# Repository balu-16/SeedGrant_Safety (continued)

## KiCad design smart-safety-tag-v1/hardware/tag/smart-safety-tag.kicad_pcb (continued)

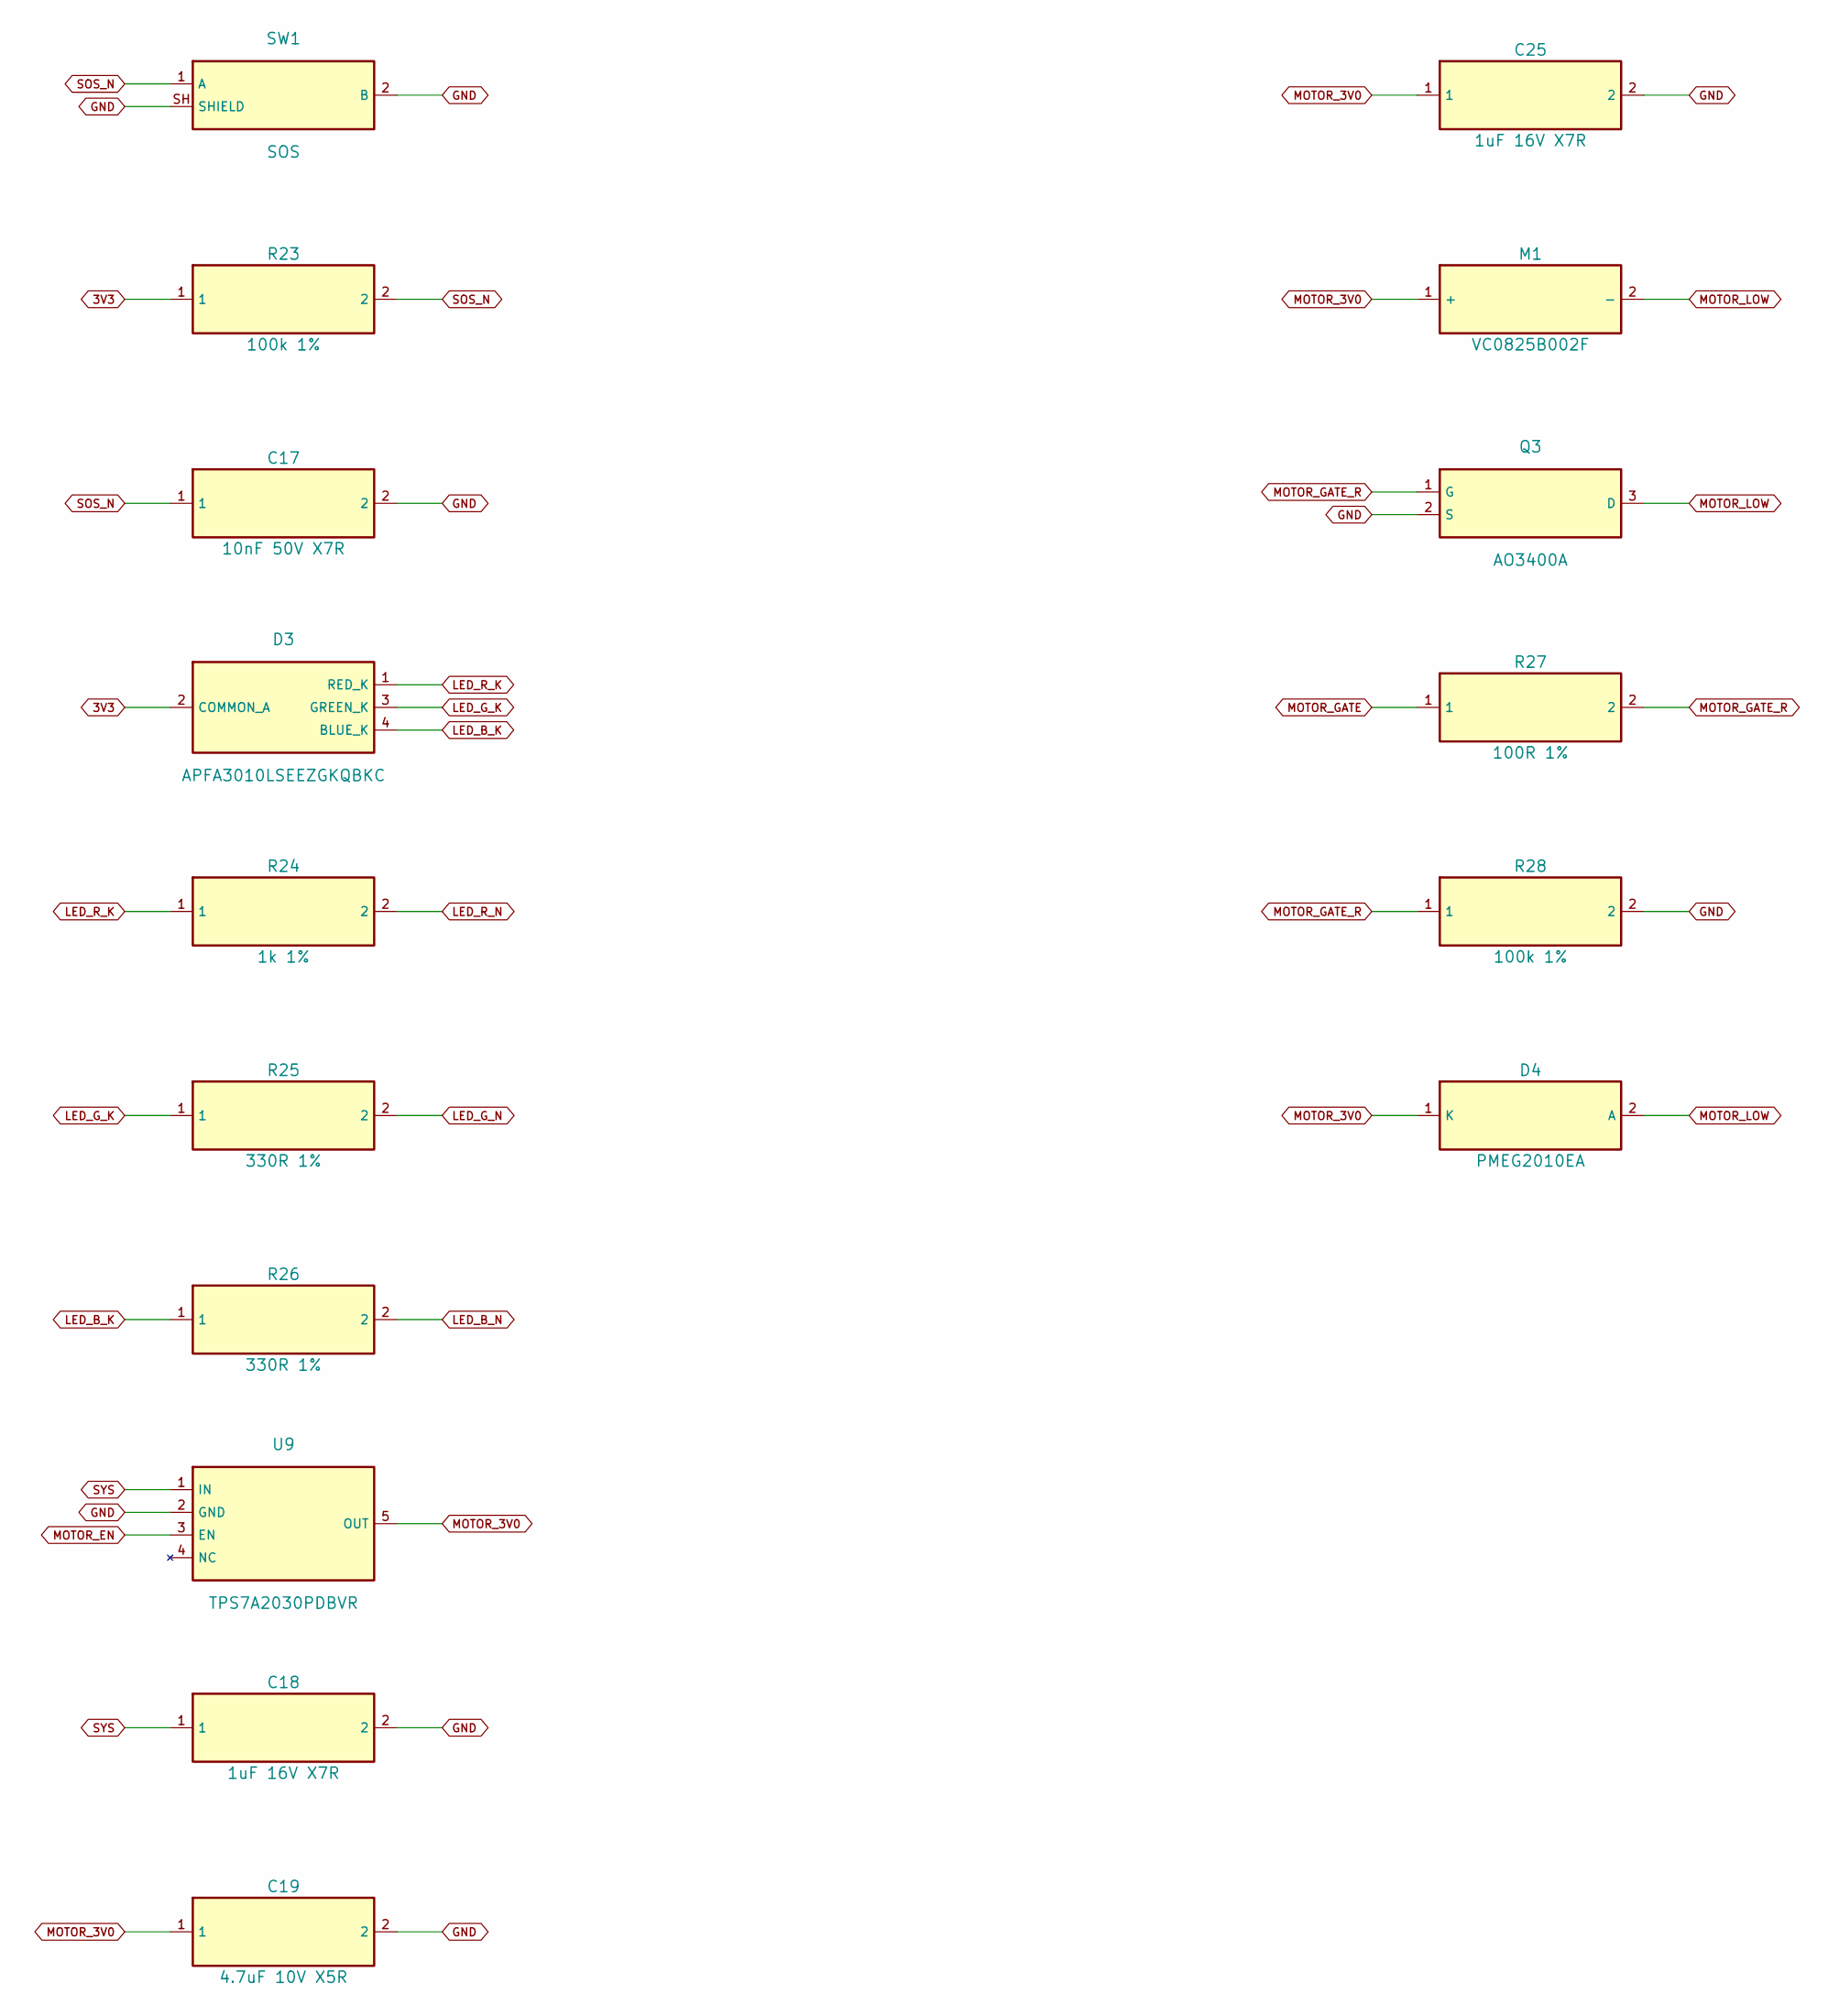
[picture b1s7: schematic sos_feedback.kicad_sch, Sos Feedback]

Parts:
C17: 10nF 50V X7R; C_0603_1608Metric; MPN C1608X7R1H103K080AA
C18, C25: 1uF 16V X7R; C_0603_1608Metric; MPN C1608X7R1C105K080AC
C19: 4.7uF 10V X5R; C_0603_1608Metric; MPN C1608X5R1A475K080AE
D3: APFA3010LSEEZGKQBKC; LED_Kingbright_APFA3010_3x1.5mm_Horizontal; MPN APFA3010LSEEZGKQBKC
D4: PMEG2010EA; D_SOD-323; MPN PMEG2010EA,115
M1: VC0825B002F; Motor_VC0825B002F; MPN VC0825B002F
Q3: AO3400A; SOT-23; MPN AO3400A
R23, R28: 100k 1%; R_0603_1608Metric; MPN RC0603FR-07100KL
R24: 1k 1%; R_0603_1608Metric; MPN RC0603FR-071KL
R25, R26: 330R 1%; R_0603_1608Metric; MPN RC0603FR-07330RL
R27: 100R 1%; R_0603_1608Metric; MPN RC0603FR-07100RL
SW1: SOS; SW_Push_1P1T-SH_NO_CK_KMR2xxG; MPN KMR231GLFS
U9: TPS7A2030PDBVR; SOT-23-5; MPN TPS7A2030PDBVR

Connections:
3V3: D3.2 (COMMON_A), R23.1; also elsewhere on the board
GND: C17.2, C18.2, C19.2, C25.2, Q3.2 (S), R28.2, SW1.2 (B), SW1.SH (SHIELD), U9.2 (GND); also elsewhere on the board
LED_B_K: D3.4 (BLUE_K), R26.1
LED_B_N: R26.2; also elsewhere on the board
LED_G_K: D3.3 (GREEN_K), R25.1
LED_G_N: R25.2; also elsewhere on the board
LED_R_K: D3.1 (RED_K), R24.1
LED_R_N: R24.2; also elsewhere on the board
MOTOR_3V0: C19.1, C25.1, D4.1 (K), M1.1 (+), U9.5 (OUT)
MOTOR_EN: U9.3 (EN); also elsewhere on the board
MOTOR_GATE: R27.1; also elsewhere on the board
MOTOR_GATE_R: Q3.1 (G), R27.2, R28.1
MOTOR_LOW: D4.2 (A), M1.2 (-), Q3.3 (D)
SOS_N: C17.1, R23.2, SW1.1 (A); also elsewhere on the board
SYS: C18.1, U9.1 (IN); also elsewhere on the board

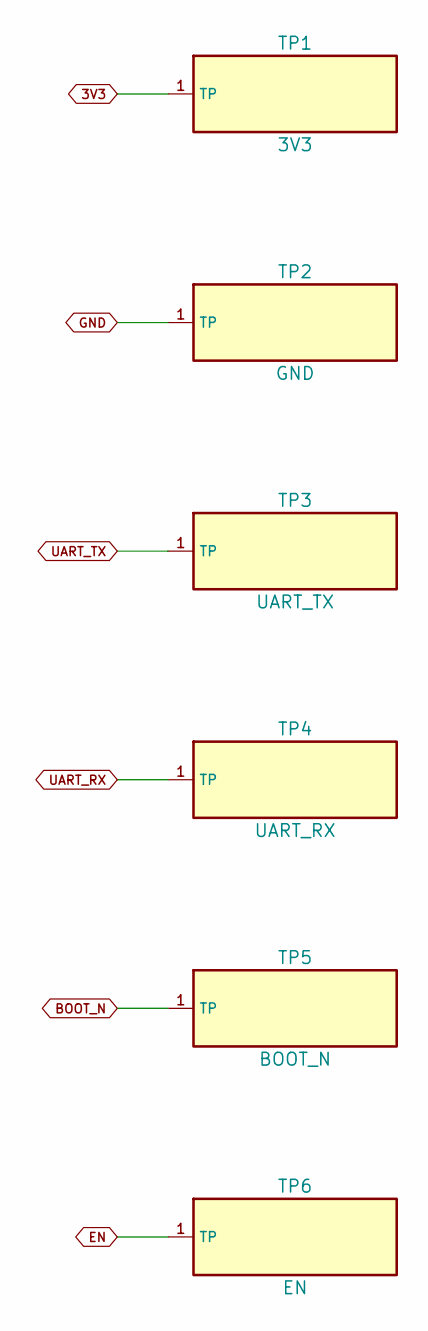
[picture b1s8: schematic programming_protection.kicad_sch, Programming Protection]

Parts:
TP1: 3V3; TestPoint_Pad_D1.0mm
TP2: GND; TestPoint_Pad_D1.0mm
TP3: UART_TX; TestPoint_Pad_D1.0mm
TP4: UART_RX; TestPoint_Pad_D1.0mm
TP5: BOOT_N; TestPoint_Pad_D1.0mm
TP6: EN; TestPoint_Pad_D1.0mm

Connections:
3V3: TP1.1; also elsewhere on the board
BOOT_N: TP5.1; also elsewhere on the board
EN: TP6.1; also elsewhere on the board
GND: TP2.1; also elsewhere on the board
UART_RX: TP4.1; also elsewhere on the board
UART_TX: TP3.1; also elsewhere on the board

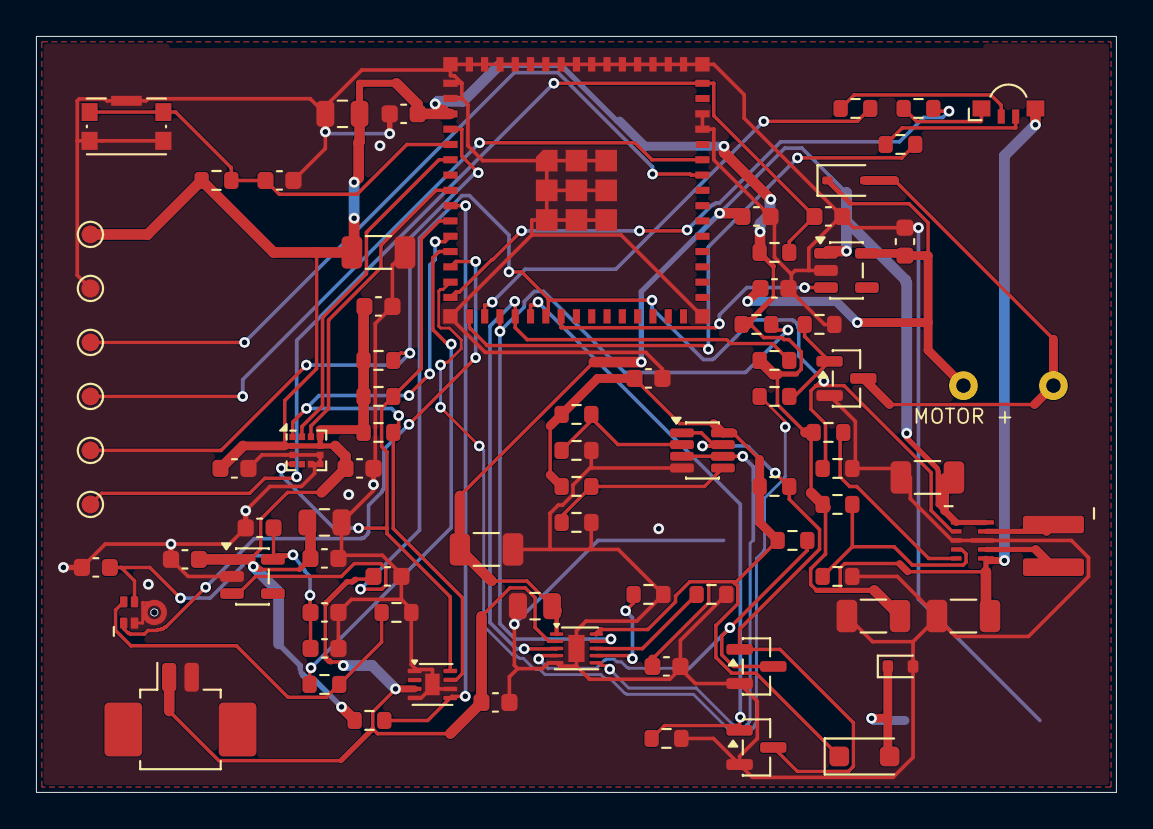
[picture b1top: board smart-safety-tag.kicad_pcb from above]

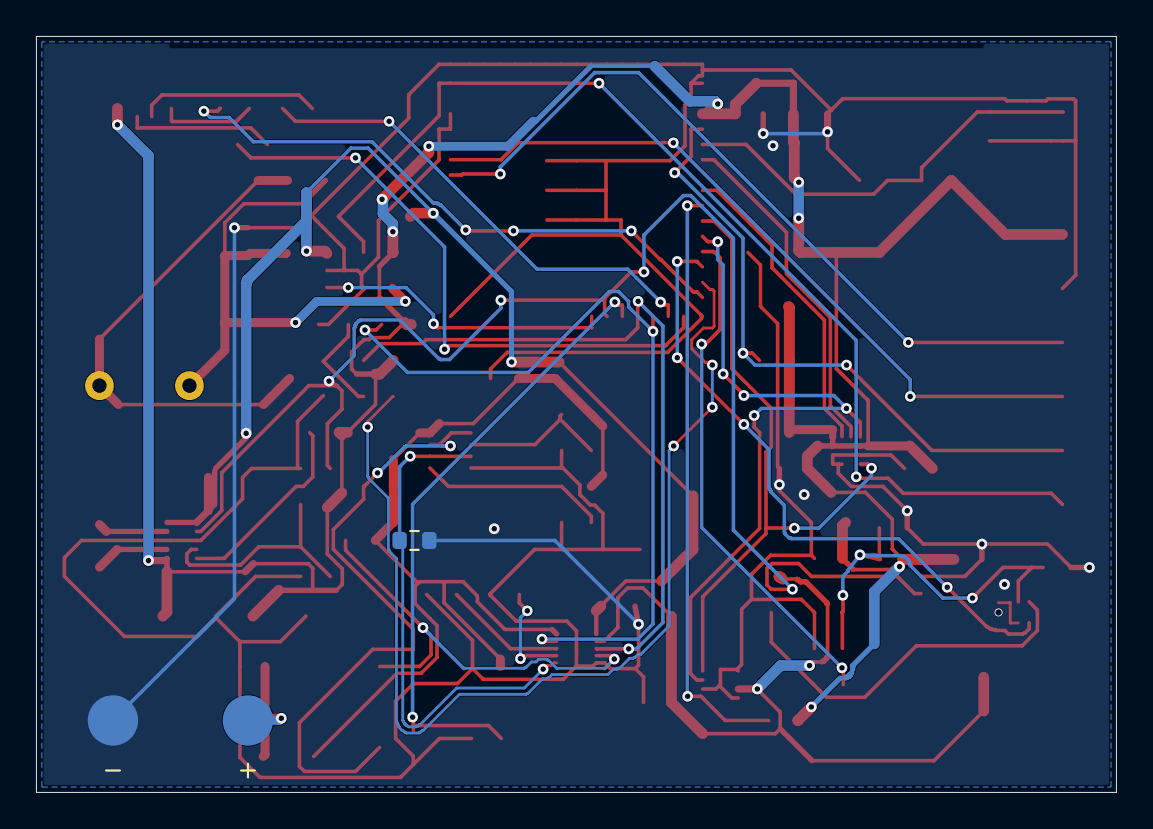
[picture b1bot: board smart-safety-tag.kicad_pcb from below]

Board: 2 copper layers, 60.0 x 42.0 mm, 83 parts (2 on the bottom side), 46 nets.

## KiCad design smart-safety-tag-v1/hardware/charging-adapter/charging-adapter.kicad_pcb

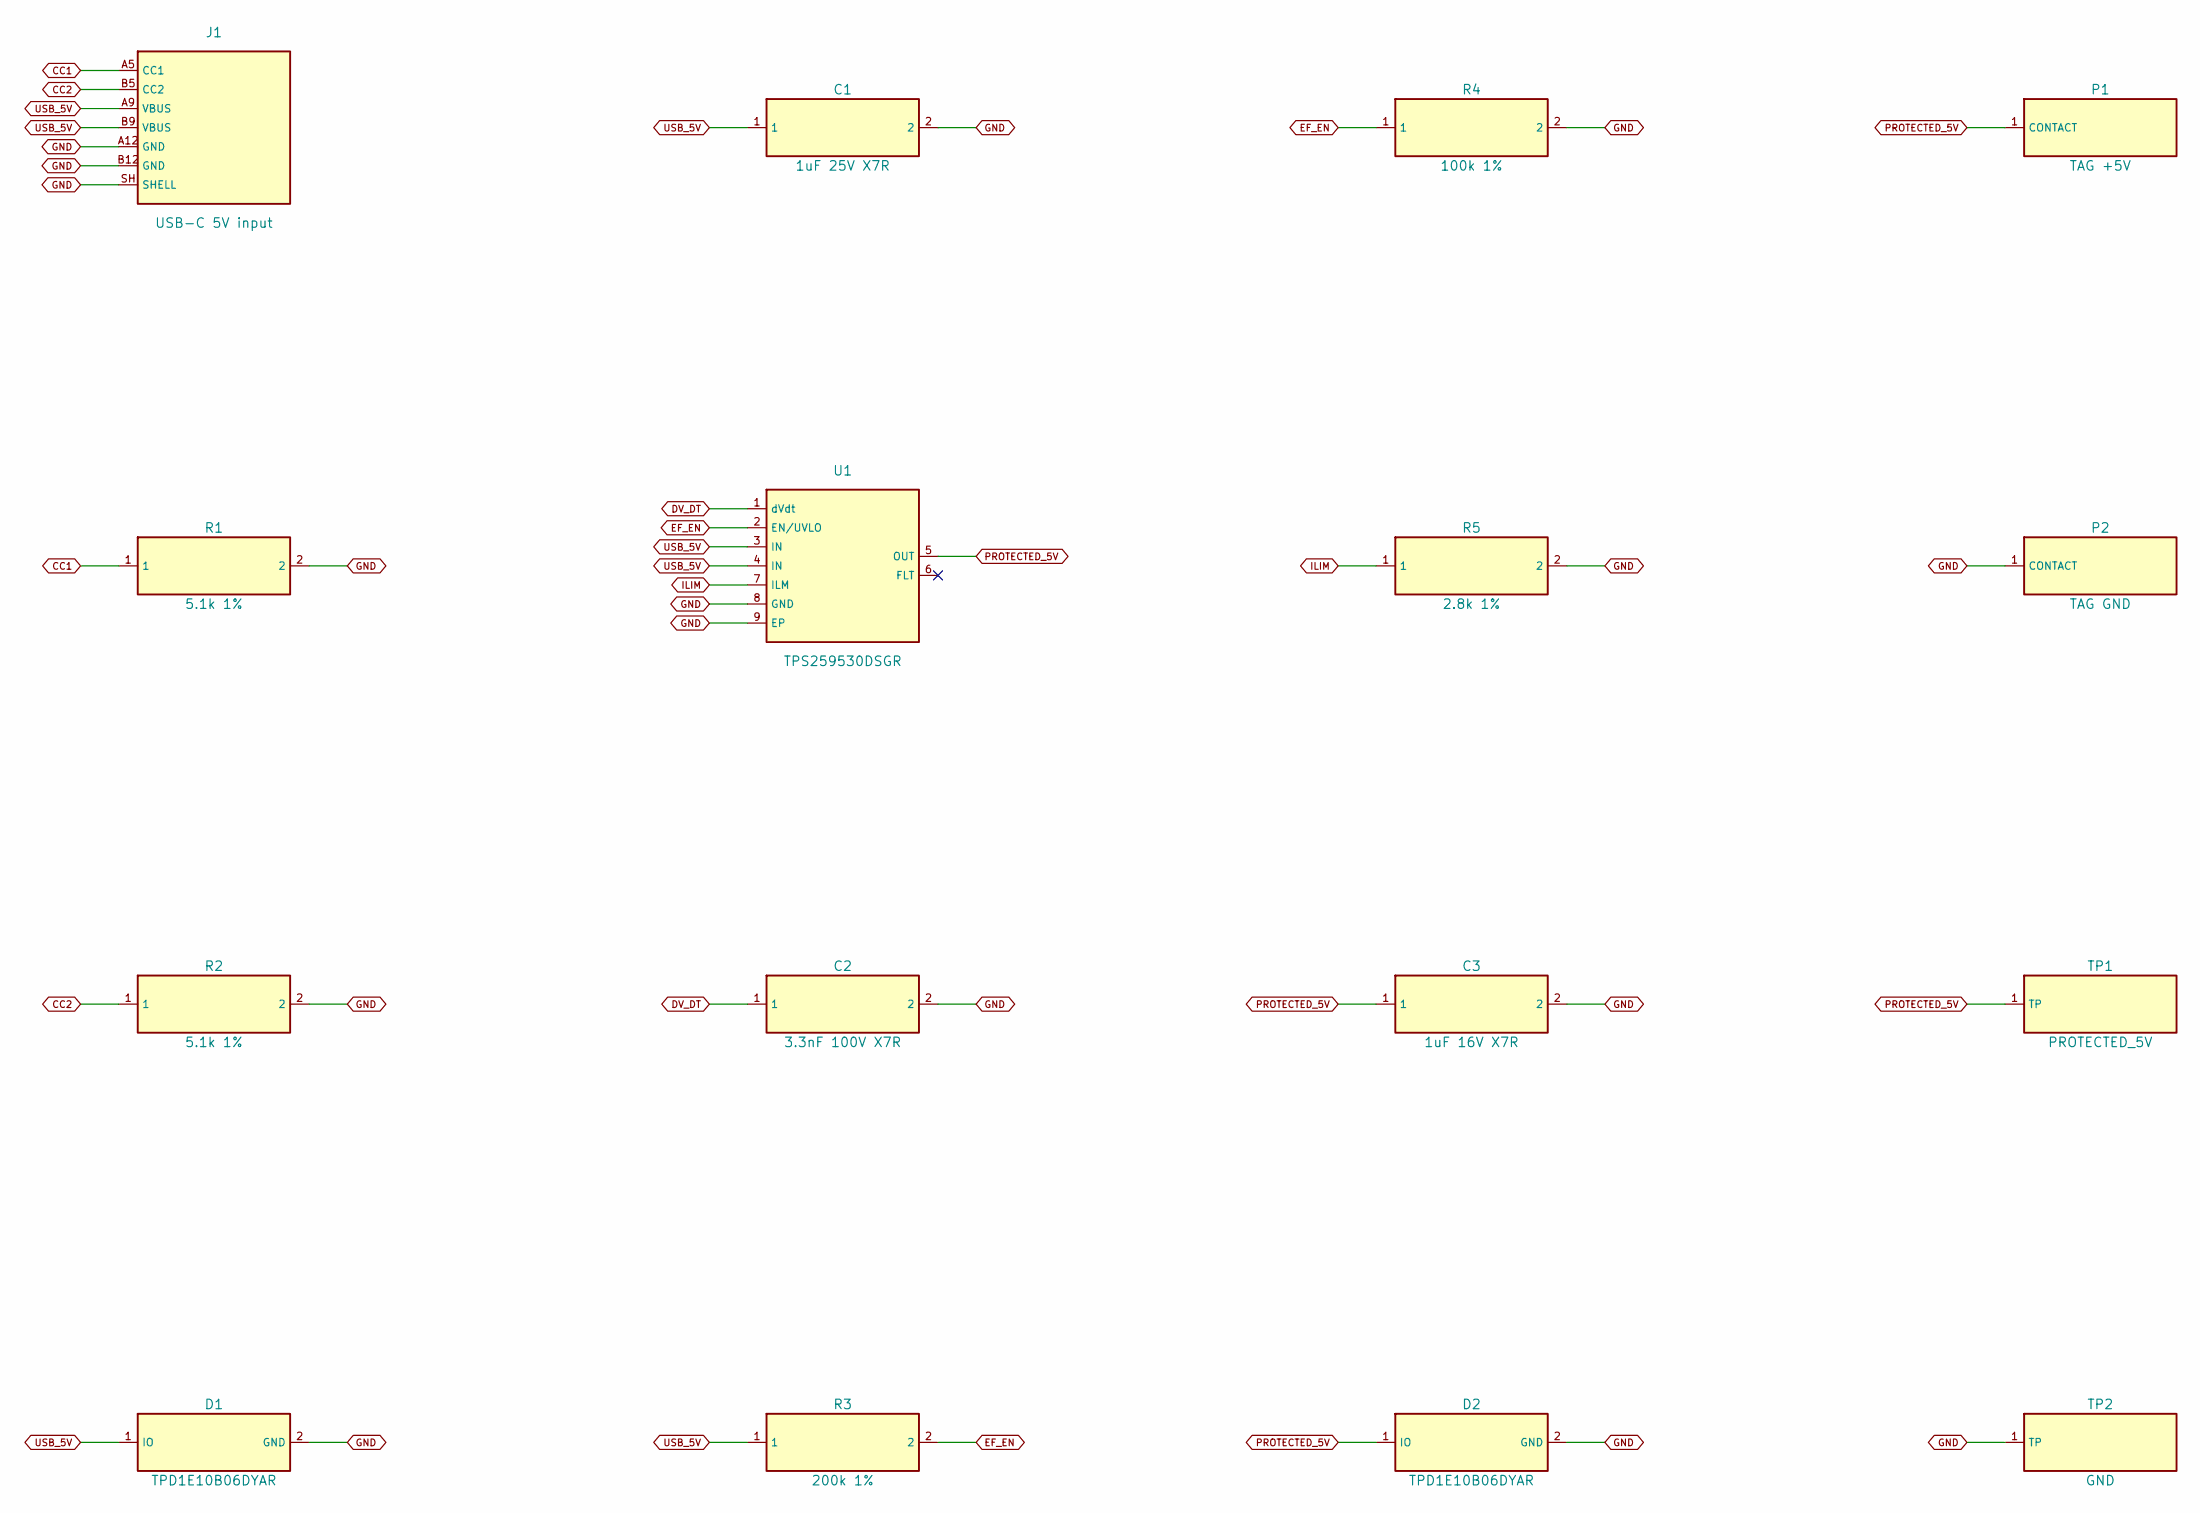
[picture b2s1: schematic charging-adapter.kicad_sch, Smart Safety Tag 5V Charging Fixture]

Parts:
C1: 1uF 25V X7R; C_0603_1608Metric; MPN C1608X7R1E105K080AE
C2: 3.3nF 100V X7R; C_0603_1608Metric; MPN C1608X7R2A332K080AA
C3: 1uF 16V X7R; C_0603_1608Metric; MPN C1608X7R1C105K080AC
D1, D2: TPD1E10B06DYAR; D_SOD-523; MPN TPD1E10B06DYAR
J1: USB-C 5V input; USB_C_Receptacle_GCT_USB4125-xx-x_6P_TopMnt_Horizontal; MPN USB4125-GF-A
P1: TAG +5V; PogoPin_MillMax_0900-1; MPN 0900-1-15-20-75-14-11-0
P2: TAG GND; PogoPin_MillMax_0900-1; MPN 0900-1-15-20-75-14-11-0
R1, R2: 5.1k 1%; R_0603_1608Metric; MPN RC0603FR-075K1L
R3: 200k 1%; R_0603_1608Metric; MPN RC0603FR-07200KL
R4: 100k 1%; R_0603_1608Metric; MPN RC0603FR-07100KL
R5: 2.8k 1%; R_0603_1608Metric; MPN RC0603FR-072K8L
TP1: PROTECTED_5V; TestPoint_Pad_D1.0mm
TP2: GND; TestPoint_Pad_D1.0mm
U1: TPS259530DSGR; Texas_DSG0008A_WSON-8-1EP_2x2mm_P0.5mm_EP0.9x1.6mm; MPN TPS259530DSGR

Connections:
CC1: J1.A5 (CC1), R1.1
CC2: J1.B5 (CC2), R2.1
DV_DT: C2.1, U1.1 (dVdt)
EF_EN: R3.2, R4.1, U1.2 (EN/UVLO)
GND: C1.2, C2.2, C3.2, D1.2 (GND), D2.2 (GND), J1.A12 (GND), J1.B12 (GND), J1.SH (SHELL), P2.1, R1.2, R2.2, R4.2, R5.2, TP2.1, U1.8 (GND), U1.9 (EP)
ILIM: R5.1, U1.7 (ILM)
PROTECTED_5V: C3.1, D2.1 (IO), P1.1, TP1.1, U1.5 (OUT)
USB_5V: C1.1, D1.1 (IO), J1.A9 (VBUS), J1.B9 (VBUS), R3.1, U1.3 (IN), U1.4 (IN)

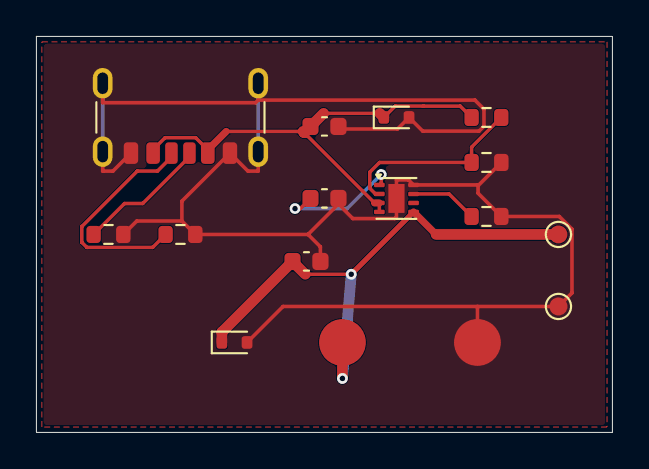
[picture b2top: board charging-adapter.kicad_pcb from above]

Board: 2 copper layers, 32.0 x 22.0 mm, 16 parts (0 on the bottom side), 8 nets.

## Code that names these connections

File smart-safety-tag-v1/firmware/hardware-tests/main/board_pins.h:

/* Generated from hardware/board-interface.json and audited against the MCU symbol. */
#pragma once

#define PIN_SOS_N 1
#define PIN_ACCELEROMETER_INT1 2
#define PIN_ACCELEROMETER_INT2 4
#define PIN_FUEL_ALERT_N 5
#define PIN_I2C_SDA 6
#define PIN_I2C_SCL 7
#define PIN_PDM_CLK 8
#define PIN_PDM_DATA 9
#define PIN_MOTOR_GATE 10
#define PIN_LED_RED_N 11
#define PIN_LED_GREEN_N 12
#define PIN_LED_BLUE_N 13
#define PIN_CHARGER_STAT1_N 14
#define PIN_CHARGER_STAT2_N 15
#define PIN_CHARGE_INHIBIT 16
#define PIN_REGULATOR_MODE 17
#define PIN_MOTOR_SUPPLY_ENABLE 18
#define PIN_UART0_TX 43
#define PIN_UART0_RX 44
#define PIN_BOOT 0

#define AUDIO_PCM_RATE_HZ 16000
#define AUDIO_PDM_CLOCK_HZ 2048000
